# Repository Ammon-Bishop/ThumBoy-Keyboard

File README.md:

This project includes all the files someone interested in building my keyboard design would need. Go ahead and build it if you're interested, I would love to see your builds!

Project is currently untested, tho, so proceed at own risk! Will update when I have tested and gotten my keyboard working.

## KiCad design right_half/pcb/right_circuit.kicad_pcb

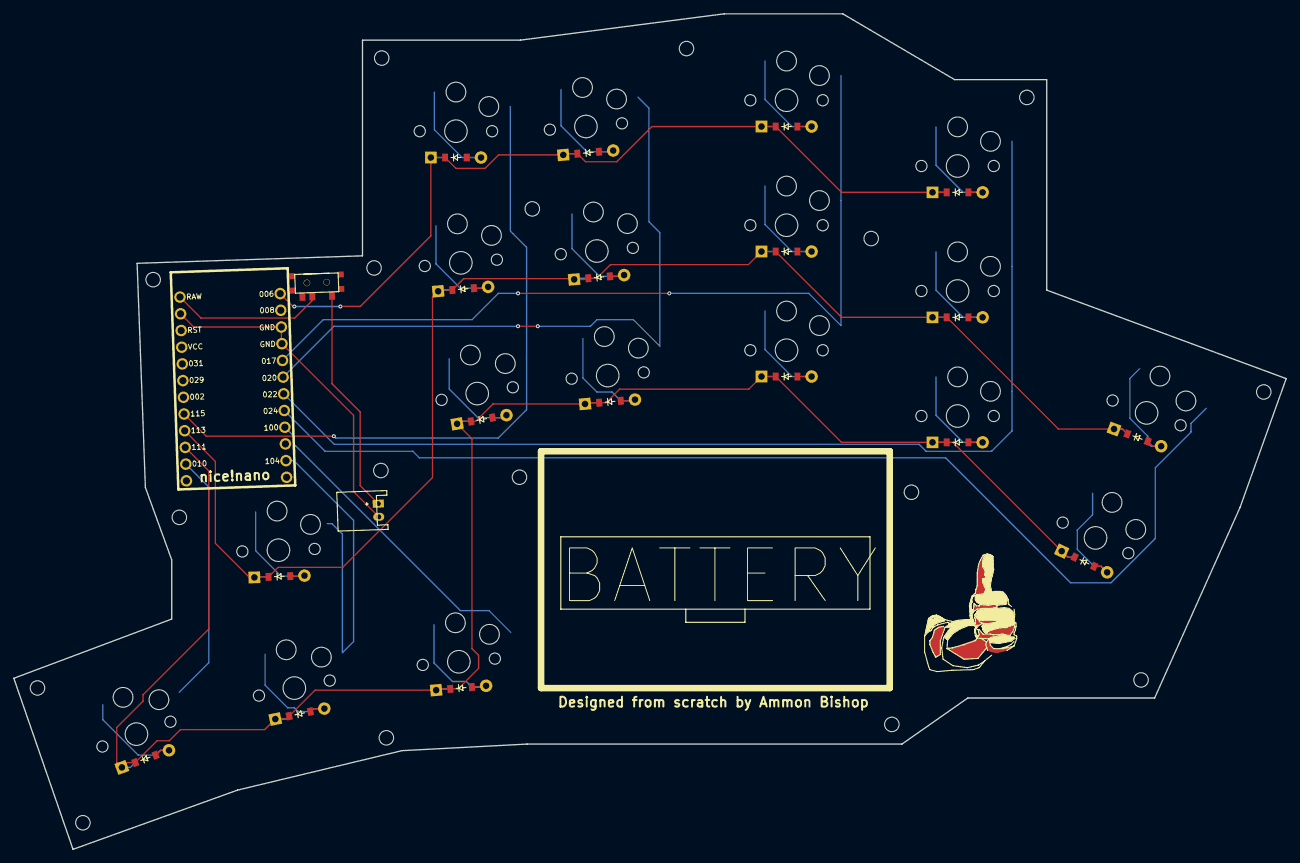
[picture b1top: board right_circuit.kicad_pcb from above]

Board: 2 copper layers, 193.4 x 127.0 mm, 56 parts (0 on the bottom side), 32 nets.

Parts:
D1, D2, D3, D4, D5, D6, D7, D8, D9, D10, D11, D12, D13, D14, D15, D16, D17, D18: ComboDiode
JST1: JST_PH_S2B-PH-K_02x2.00mm_Angled
MCU1: nice_nano
MH1, MH1#2, MH1#3, MH1#4, MH1#5, MH1#6, MH1#7, MH1#8, MH1#9, MH1#10, MH1#11, MH1#12, MH1#13, MH1#14, MH1#15, MH1#16, MH1#17: mounting_hole_npth
S1, S2, S3, S4, S5, S6, S7, S8, S9, S10, S11, S12, S13, S14, S15, S16, S17, S18: PG1350
T1: SPDT_C128955

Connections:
GND: JST1.2, MCU1.3, MCU1.4, MCU1.23
P006: D7.1, D10.1, D13.1, D16.1, MCU1.1
P010: MCU1.14, S1.2
P017: MCU1.5, S11.2, S12.2, S13.2
P020: MCU1.6, S8.2, S9.2, S10.2
P022: MCU1.7, S14.2, S15.2, S16.2
P024: MCU1.8, S17.2, S18.2
P100: MCU1.9, S4.2
P104: MCU1.11, S2.2, S3.2
P111: D1.1, D2.1, D4.1, D5.1, D8.1, D11.1, D14.1, D17.1, MCU1.15
P113: D3.1, D6.1, D9.1, D12.1, D15.1, D18.1, MCU1.16
P115: MCU1.17, S5.2, S6.2, S7.2
RAW: MCU1.24, T1.2
four_bottom: D8.2, S8.1
four_home: D9.2, S9.1
four_top: D10.2, S10.1
inner_bottom: D5.2, S5.1
inner_home: D6.2, S6.1
inner_top: D7.2, S7.1
one_bottom: D17.2, S17.1
one_home: D18.2, S18.1
pos: JST1.1, T1.1
three_bottom: D11.2, S11.1
three_home: D12.2, S12.1
three_top: D13.2, S13.1
thumb-inner_bottom: D4.2, S4.1
thumb-outer_bottom: D1.2, S1.1
thumb_bottom: D2.2, S2.1
thumb_home: D3.2, S3.1
two_bottom: D14.2, S14.1
two_home: D15.2, S15.1
two_top: D16.2, S16.1

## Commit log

2025-01-07 Create -
2025-01-07 Create same
